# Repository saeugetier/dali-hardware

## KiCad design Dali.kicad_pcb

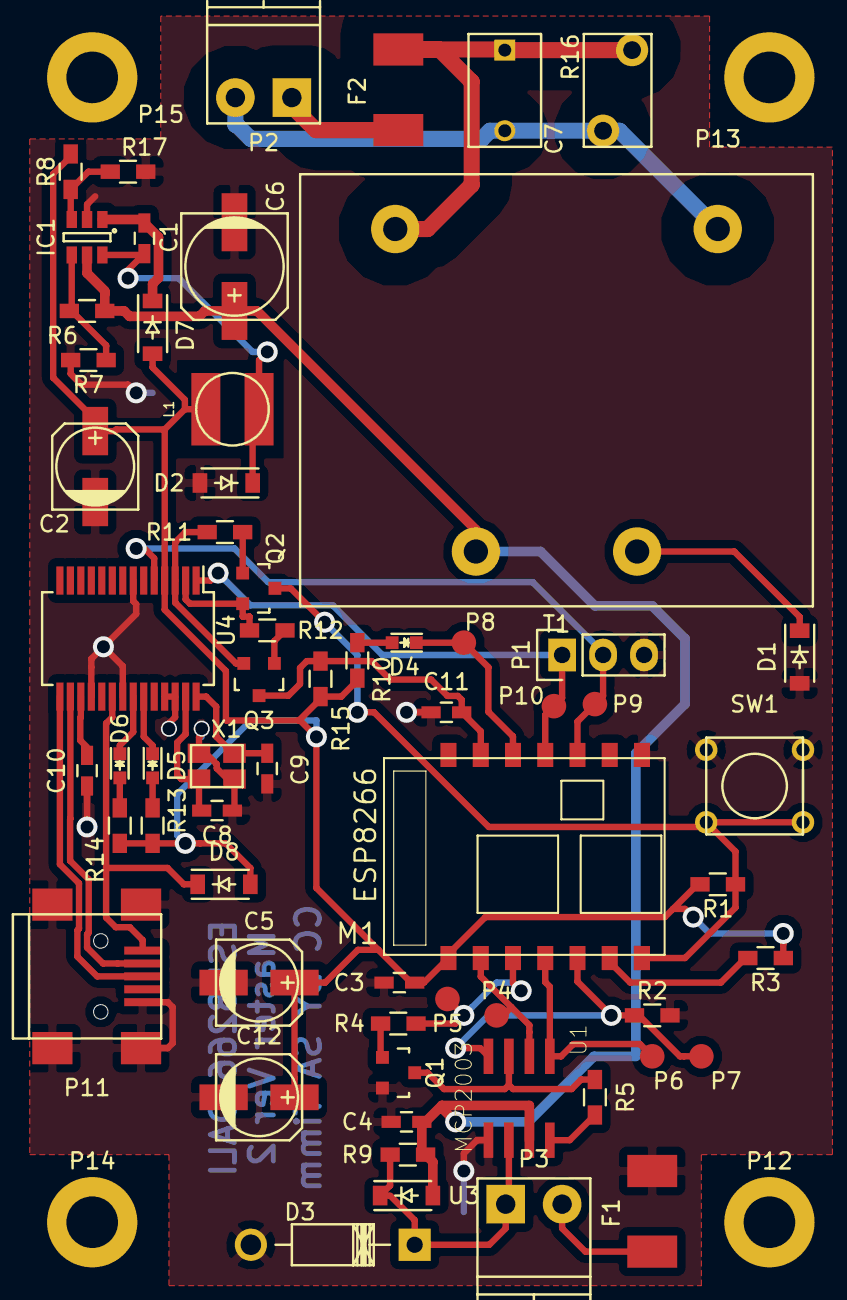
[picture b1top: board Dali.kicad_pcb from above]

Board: 2 copper layers, 66 parts (0 on the bottom side), 41 nets.

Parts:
C1: 100n; C_0603_HandSoldering
C2, C5, C12: CP; c_elec_5x5.3
C3: 100nF; C_0603_HandSoldering
C4: 220p; C_0603_HandSoldering
C6: CP; c_elec_6.3x7.7
C7: C; C_Rect_L7_W4.5_P5
C8, C9, C10: C; C_0603_HandSoldering
C11: 470pF; C_0603_HandSoldering
D1, D2, D7, D8: D_Schottky; SOD-123
D3: ZENER; Diode_DO-41_SOD81_Horizontal_RM10
D4, D5, D6: LED; LED_0603
F1: F_Small; FUSE_2410
F2: FUSE; FUSE_2410
IC1: LMR14206; SOT-23-6
L1: INDUCTOR; BOURNS-SDR0403
M1: ESP8266; ESP8266-ESP-03
P1: CONN_01X03; Pin_Header_Straight_1x03
P2, P3: CONN_01X02; TerminalBlock_Pheonix_PT-3.5mm_2pol
P4, P5, P6, P7, P8, P9, P10: TST; Measurement_Point_Round-SMD-Pad_Small
P11: USB_OTG; USB_Mini-B
P12, P13, P14, P15: CONN_01X01; MountingHole_3.2mm_M3_DIN965_Pad
Q1, Q2, Q3: Q_NPN_BEC; SOT-23
R1, R2, R3, R15: 12k; R_0603_HandSoldering
R4, R5, R9: R; R_0603_HandSoldering
R6: 4,7k; R_0603_HandSoldering
R7: 2k; R_0603_HandSoldering
R8: 34k; R_0603_HandSoldering
R10, R13, R14: 330; R_0603_HandSoldering
R11, R12: 12K; R_0603_HandSoldering
R16: RVAR; RV_Disc_D7_W4.2_P5_Big
R17: 10k; R_0603_HandSoldering
SW1: SW_PUSH; SW_PUSH_SMALL
T1: TRANSFO; VTX-214-003-115
U1: MCP2003; SO-08
U3: CRD; SOD-123
U4: FT232RL; SSOP-28_5.3x10.2mm_Pitch0.65mm
X1: CRYSTAL_SMD; crystal_FA238-TSX3225

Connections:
+3V3: C2.1, C3.1, C5.1, C12.1, D7.2, D8.2, L1.1, M1.VCC, R1.1, R3.2, R8.2, R10.1, R13.2, R14.2, R15.2, U4.4
+5V: D8.1, P11.1, U4.20
CS: M1.GP14, P4.1, U1.2
FLASH: M1.GP0, Q2.3, R1.2, SW1.2
GND: C2.2, C3.2, C4.2, C5.2, C6.2, C8.1, C9.1, C10.1, C11.1, C12.2, D1.2, D2.2, D3.2, F1.1, IC1.2, M1.GND, P1.3, P11.5, P11.6, Q1.2, R2.2, R7.1, R17.1, SW1.1, U1.5, U4.7, U4.18, U4.21, U4.25, U4.26, X1.3
unnamed: C1.1, D7.1, IC1.1
unnamed: C1.2, D2.1, IC1.6, L1.2
unnamed: C4.1, C6.1, IC1.5, R6.2, R9.1, T1.3, U1.7, U3.2
unnamed: C7.1, F2.1, R16.1, T1.2
unnamed: C7.2, P2.2, R16.2, T1.1
unnamed: C8.2, U4.27, X1.1
unnamed: C9.2, U4.28, X1.2
unnamed: C10.2, U4.17
unnamed: D1.1, T1.4
unnamed: D3.1, P3.1, R9.2, U1.6, U3.1
unnamed: D4.1, M1.GP18, P8.1
unnamed: D4.2, R10.2
unnamed: D5.1, U4.23
unnamed: D5.2, R13.1
unnamed: D6.1, U4.22
unnamed: D6.2, R14.1
unnamed: F1.2, P3.2
unnamed: F2.2, P2.1
unnamed: IC1.3, R8.1, R17.2
unnamed: IC1.4, R6.1, R7.2
unnamed: M1.GP2, R3.1
unnamed: P11.2, U4.16
unnamed: P11.3, U4.15
unnamed: Q1.1, R4.2
unnamed: Q1.3, R5.1, U1.3
unnamed: Q2.1, R11.2
unnamed: Q2.2, R12.1, U4.2
unnamed: Q3.1, R12.2
unnamed: Q3.2, R11.1, U4.3
unnamed: R5.2, U1.8
RST: C11.2, M1.CH_P, Q3.3, R15.1
RXD: M1.GP13, P6.1, U1.1
TXD: M1.GP15, P7.1, R2.1, U1.4
URXD: M1.URXD, P1.1, P10.1, U4.1
UTXD: M1.UTXD, P1.2, P9.1, U4.5
WAKE: M1.GP12, P5.1, R4.1

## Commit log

2016-05-31 working on version. before changing voltage regulator
2016-05-31 added two missing files
2016-11-27 latest production state

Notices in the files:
Dali.kicad_pcb:
CC BY SA Timm
